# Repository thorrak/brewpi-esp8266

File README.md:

# BrewPi-ESP
An implementation of the BrewPi firmware on the ESP8266, ESP32, and ESP32-S2 with additional, added features

## Introduction
BrewPi provides a temperature controller which uses PID algorithms to tightly control a fermenting beer's temperature -- meaning that you can in many cases control the temperature of your fermenting beer to within _one tenth of a degree_. It was originally designed by Elco Jacobs, and used an Arduino running the BrewPi firmware to measure temperatures and toggle heating/cooling, paired with a Raspberry Pi to receive & graph temperature changes over time.

This project ports the BrewPi firmware to the ESP8266, ESP32, and ESP32-S2 controllers, eliminating the need for an Arduino. It is compatible with [Fermentrack 2/Fermentrack.net](https://www.fermentrack.net/), [legacy Fermentrack](http://www.fermentrack.com/) and [BrewPi-Remix](https://www.brewpiremix.com/) - the latter two of which can be installed on a Raspberry Pi to capture/graph temperatures similar to the original project.

> **Note:** ESP8266 support is deprecated as of the upcoming release. Existing ESP8266 builds will continue to receive bug fixes for a limited time, but new features will only target the ESP32 and ESP32-S2. For existing builds using the LoLin D1 Mini, the LoLin S2 Mini (ESP32-S2) is a pin-compatible replacement. See the [ESP8266 pinout](#esp8266) section below for more details.

### Documentation:
* [Selecting your Hardware](docs/source/Selecting%20an%20ESP%20Board.md)  
* [Building a "Solder Free" BrewPi](docs/source/Solder%20Free%20BrewPi.md)  
* [Installing the Firmware](docs/source/Installing%20the%20Firmware.md)
* [Hardware Information](https://github.com/thorrak/thorrak_hardware/tree/master/ESP8266%20BrewPi%20Boards) - PCB files, ordering and BOMs

## Configuration
Once you've flashed firmware to your ESP device, you'll need to configure it to connect to your WiFi network.  For that purpose, the firmware creates a WiFi access point named `BrewPiAP`, with a password of `brewpiesp`.  Connect to that access point and, if your device doesn't pull up a configuration page on its own, browse to `http://192.168.4.1`.  Then click on **Configure WiFi,** and configure it to connect to your WiFi network.

## Expected Pinout

### ESP32

There are two versions of the ESP32 firmware - one supporting an LCD2004 I2C display and one supporting a TFT. The pinout is slightly different between the two:

#### Common Pins

* 25 - Heat
* 26 - Cool
* 13 - OneWire Data
* 34 - Door

#### I2C Pins

* 21 - I2C SDA
* 22 - I2C SCL

#### TFT Pins

* 14 - TFT CS
* 27 - TFT DC
* 33 - TFT RST
* 12 - TS CS
* 32 - TFT Backlight

### ESP32-S2

* 5 - Heat
* 7 - Cool
* 9 - OneWire Data
* 11 - Door
* 33 - I2C SDA
* 35 - I2C SCL

### ESP8266 (Deprecated)

> **Deprecated:** ESP8266 support is deprecated and will not receive new features following v16. For existing builds using the LoLin D1 Mini, the [LoLin S2 Mini](https://www.aliexpress.us/item/3256802958877264.html) (ESP32-S2) is a pin-compatible drop-in replacement.

* D0 - Heat
* D1 - I2C SCL
* D2 - I2C SDA
* D5 - Cool
* D6 - OneWire Data
* D7 - Door (Untested)

## Supported Features
* OneWire Temperature Sensors
* SPIFFS configuration saving
* Pin-Based Relays
* WiFi Soft-AP Configuration
* OTA (WiFi) connection to BrewPi 
* I2C LCD (20x4) Screen (/w Address Autodetection)
* Tilt Hydrometer (as Temp Sensor) (ESP32 only)
* Inkbird Bluetooth temperature sensors (ESP32 only)
* TPLink Kasa WiFi Switches (ESP32 & ESP32-S2 WiFi only)
* HTTP interface for quick updates

## Currently Unsupported/Untested
* Rotary Encoder Support
* Door Sensor Support (Note - May work, untested)
* Buzzer Support
* OneWire "actuators"

## Differences vs. Arduino Implementation
The primary goal in creating this was to mirror the spirit of the Arduino implementation as closely as possible while adding in support for WiFi. That said, where I've needed to decide between preserving the original code and adapting for use with ESP controllers I've generally erred towards the latter. This is especially true with the EEPROM code - this implementation completely replaces the EEPROM with SPIFFS.

## Fermentrack Integration

Although this firmware works with brewpi-www, it is highly recommended that users use [Fermentrack 2/Fermentrack.net](https://www.fermentrack.net/) or [legacy Fermentrack](http://www.fermentrack.com/) instead as Fermentrack substantially reduces the work required to get an ESP-based controller working. Ongoing testing & support for this firmware is exclusively performed on Fermentrack and future changes may introduce incompatibility with brewpi-www.

## Hardware

I maintain a separate repo with PCB and 3D-printable case designs for all of my projects. It is available [here](https://github.com/thorrak/thorrak_hardware/).

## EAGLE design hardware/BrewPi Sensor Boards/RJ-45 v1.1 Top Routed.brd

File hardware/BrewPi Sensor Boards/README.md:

BrewPi Sensor Boards
====================

The BrewPi sensor boards are intended to allow for the DS18b20 temperature sensors (and optionally, door switch) to be connected to a PCB that is away from your main BrewPi controller, thereby allowing for the use of shorter temperature sensor cables - or for the placement of the sensor breakout inside your fermentation chamber if necessary. The sensor boards are then intended to be connected to the main controller board through the use of a cable.

There are two versions of the board, RJ-11 and RJ-45 -- however the RJ-45 version is recommended in nearly 100% of cases. 

* [RJ-45 Breakout Board](RJ-45%20Sensor%20Breakout.md)

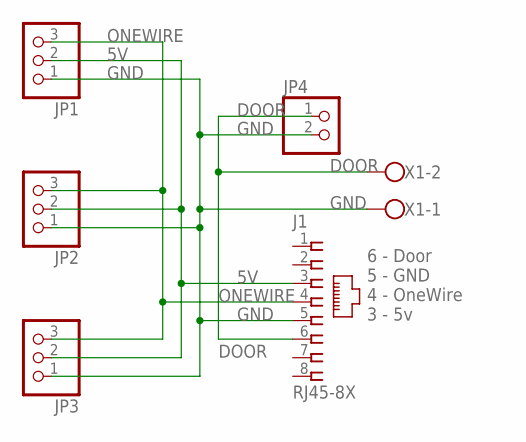
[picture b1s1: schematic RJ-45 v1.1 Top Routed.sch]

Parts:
J1: RJ45-8X; RJ45-NO-SHIELD
JP1, JP2, JP3: PINHD-1X3; 1X03
JP4: PINHD-1X2; 1X02
X1: W237-102

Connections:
5V: J1.3, JP1.2, JP2.2, JP3.2
DOOR: J1.6, JP4.1, X1.2
GND: J1.5, JP1.1, JP2.1, JP3.1, JP4.2, X1.1
ONEWIRE: J1.4, JP1.3, JP2.3, JP3.3

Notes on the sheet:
6 - Door 5 - GND 4 - OneWire 3 - 5v

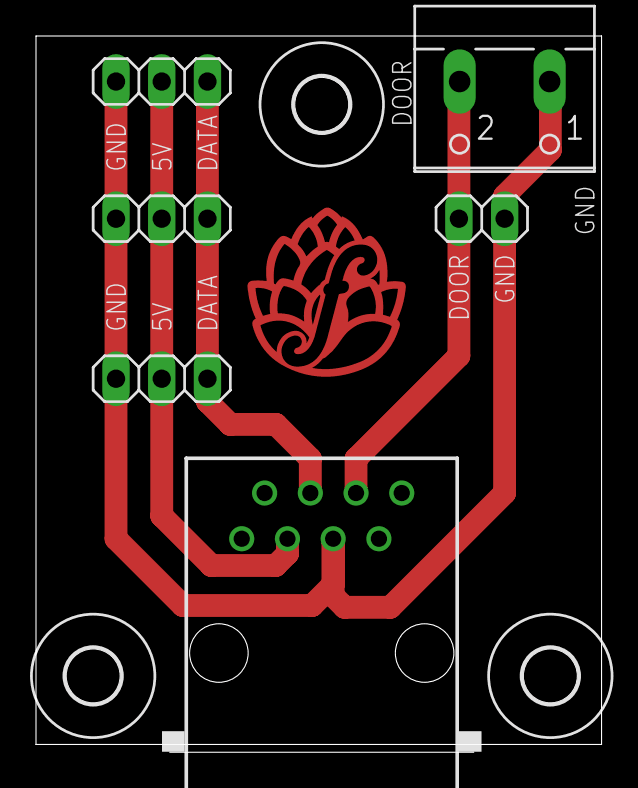
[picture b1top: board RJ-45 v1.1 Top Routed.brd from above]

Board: 2 copper layers, 31.4 x 39.8 mm, 9 parts (0 on the bottom side), 4 nets.

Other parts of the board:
U$1, U$2, U$3: 3,0

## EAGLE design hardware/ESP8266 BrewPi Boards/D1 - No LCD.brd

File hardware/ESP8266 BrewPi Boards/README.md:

ESP8266 BrewPi Controller Boards
================================

Although the "heart" of a BrewPi controller is the microprocessor running the BrewPi-compatible firmware, without other connected components that microcontroller cannot sense temperature, control power, or do any of the other things that make a temperature controller useful. Several PCBs have been designed to help simplify the wiring of the microcontroller to those other components.

Five different versions of the main PCB are listed here.  Each provide
different functionality and/or form factors:

*   No LCD Support with DuPont connectors and through-hole components
*   LCD Support with DuPont connectors and surface-mount level converter components
*   LCD Support with DuPont connectors, through-hole components, and a SparkFun-based level converter sub-board
*   LCD Support with screw connectors, through-hole components, and a SparkFun-based level converter sub-board
*   LCD Support with DuPont connectors, through-hole components, and an integrated level converter

You may either purchase the boards using the links provided through pcbs.io, or you may download and use the Eagle files provided with a board supplier of your choice.  If you use the pcbs.io links, Thorrak will receive a small credit on the site.

The BOM links provided are intended to serve as examples of the parts needed and are not the only place to source the parts listed.  Generally speaking, AliExpress is less expensive for parts.  The trade-off is that sometimes you are buying 100 at a time, and in most cases you are waiting for shipping.  Mouser or other project part suppliers will probably have these parts as well.

| Board Design                                                                             | Order Link                           | Through Hole       | Surface Mount      | I2C LCD            | Connector Type  | Integrated Level Shifter |
|------------------------------------------------------------------------------------------|--------------------------------------|--------------------|--------------------|--------------------|-----------------|--------------------------|
| Surface Mount                                                                            | [Order](https://PCBs.io/share/8DDk0) |                    | :heavy_check_mark: | :heavy_check_mark: | Dupont          | :heavy_check_mark:       |
| [TH - Sparkfun /w Dupont](D1%20-%20LCD%20TH%20Dupont.md)                                 | [Order](https://PCBs.io/share/40D1X) | :heavy_check_mark: |                    | :heavy_check_mark: | Dupont          |                          |
| [TH - MOSFETs](https://github.com/brewpi-remix/brewpi-pcb-rmx/tree/master/D1%20Breakout) | [Order](https://pcbs.io/share/z5JLZ) | :heavy_check_mark: |                    | :heavy_check_mark: | Dupont          | :heavy_check_mark:       |
| [TH - Sparkfun /w Screw Terminals](D1%20-%20LCD%20TH%20Screws.md)                        | [Order](https://PCBs.io/share/4qpVq) | :heavy_check_mark: |                    | :heavy_check_mark: | Screw Terminals |                          |
| [TH - No LCD](D1%20-%20No%20LCD.md)                                                      | [Order](https://PCBs.io/share/49yVo) | :heavy_check_mark: |                    |                    | Screw Terminals |                          |

Features Explained
------------------

### Through Hole vs. Surface Mount

Through Hole components generally have a wire or pin that goes through a hole on the PCB, enabling easy soldering on the back-side of the circuit board. By contrast, Surface Mount components are attached directly to the surface of a PCB with small dots of solder. The overwhelming majority of PCBs use primarily surface mount components - but as these are more difficult to solder by hand, many hobbyists prefer hand-soldering through hole components. 

Choose "surface mount" if you want a compact board and are comfortable with learning to solder surface mount components. Choose "through hole" if you are not comfortable soldering and would prefer the easiest option.

### I2C LCD

The ESP8266 port of the BrewPi firmware supports the utilization of a LCD screen connected via an "I2C" interface. Due to the nature of these LCD screens, this requires additional hardware which increases the size & complexity of the board - but the slight amount of additional pain when building the controller pays off in the increased utility of having an LCD display.

Choose this option if you want an LCD screen. Ignore this option if you prefer the cheapest board available (and are OK with not having an LCD display).

### Connector Type - Dupont vs. Screw Terminals

"Dupont" cables are a type of cable that has a single female header at each end. This allows for connecting two devices with "pin header" interfaces through the use of a compact "ribbon"-type cable. 

Boards that are "dupont" style have compact pin-headers on them, and can only be used with Dupont cables. By contrast, "screw terminal" style boards are designed to have screw terminals soldered on which makes attaching/detaching cables easier. Screw-terminal boards are larger but can be optionally used with pin headers as well, however "dupont" style boards are not compatible with screw terminals.

Choose "dupont" if you want a cheaper, smaller board. Choose "screw terminals" if you prefer much larger soldering pads. 

### Integrated Level Shifter

I2C LCDs require that the 3.3 volt logic from the ESP8266 be "translated" to the 5 volt logic required by the LCD. This is done through the use of a "level shifter". Level shifters are relatively simple components, but require soldering a number of things by hand which some hobbyists would prefer not to do. The boards with integrated level shifters have these additional components as part of the PCB, while those boards without an integrated level shifter use a "sparkfun"-style level shifter which is attached to the board using pin headers. 

Choose this option if you want a smaller, more compact board.

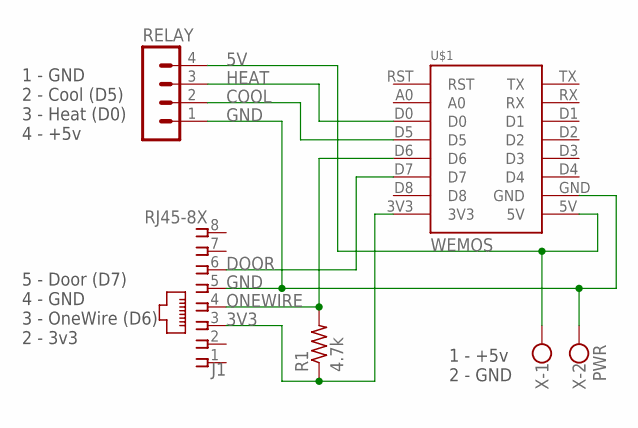
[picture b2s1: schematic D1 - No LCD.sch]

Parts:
J1: RJ45-8X; RJ45-NO-SHIELD
R1: 4.7k; 0309/12
RELAY: MA04-1
U$1: WEMOS
X: PWR; W237-102

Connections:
3V3: J1.3, R1.1, U$1.3V3
5V: RELAY.4, U$1.5V, X.1
COOL: RELAY.2, U$1.D5
DOOR: J1.6, U$1.D7
GND: J1.5, RELAY.1, U$1.GND, X.2
HEAT: RELAY.3, U$1.D0
ONEWIRE: J1.4, R1.2, U$1.D6

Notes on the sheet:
1 - GND 2 - Cool (D5) 3 - Heat (D0) 4 - +5v
5 - Door (D7) 4 - GND 3 - OneWire (D6) 2 - 3v3
1 - +5v 2 - GND

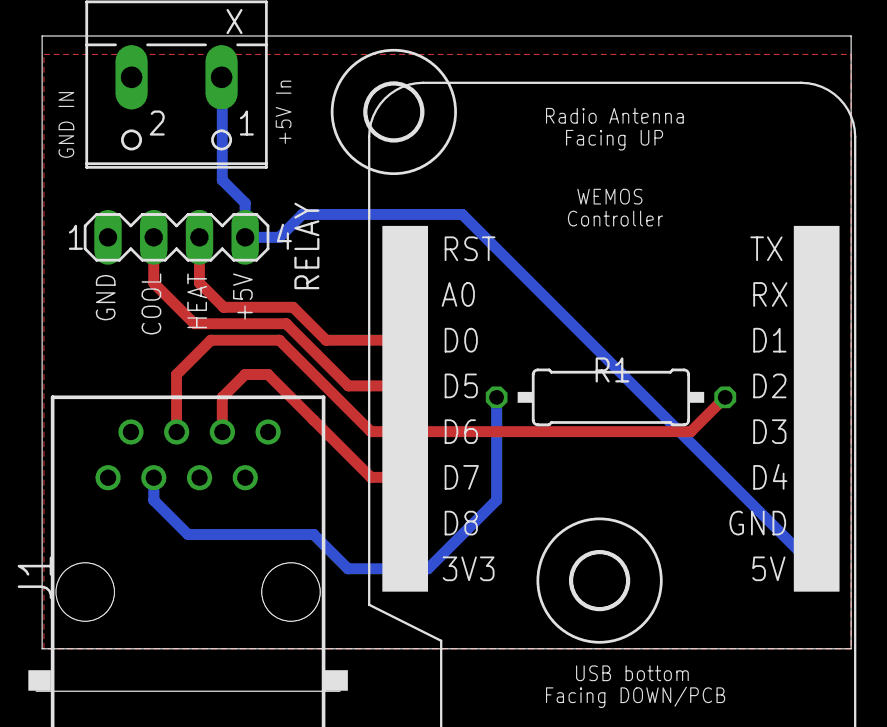
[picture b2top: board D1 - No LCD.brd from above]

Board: 2 copper layers, 45.3 x 36.4 mm, 7 parts (0 on the bottom side), 7 nets.

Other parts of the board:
U$4, U$5: 3,0

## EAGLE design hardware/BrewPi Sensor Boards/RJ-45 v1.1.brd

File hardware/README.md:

# Hardware

In the interest of streamlining updates to the PCBs, I've broken all of my "hardware" out into its own repo. For hardware related to this project, please visit:

https://github.com/thorrak/thorrak_hardware/blob/master/BrewPi-ESP8266.md

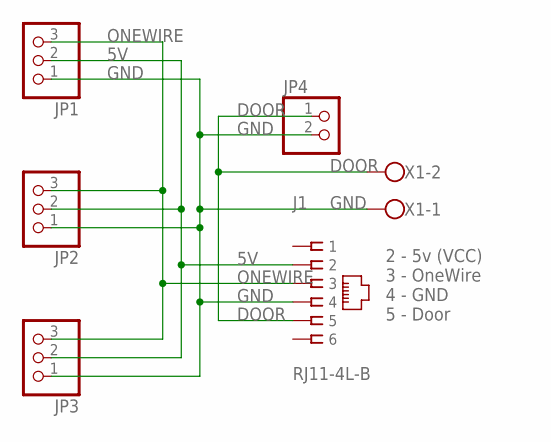
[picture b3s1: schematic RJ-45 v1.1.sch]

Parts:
J1: RJ11-4L-B; RJ11-NO_SHIELD
JP1, JP2, JP3: PINHD-1X3; 1X03
JP4: PINHD-1X2; 1X02
X1: W237-102

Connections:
5V: J1.2, JP1.2, JP2.2, JP3.2
DOOR: J1.5, JP4.1, X1.2
GND: J1.4, JP1.1, JP2.1, JP3.1, JP4.2, X1.1
ONEWIRE: J1.3, JP1.3, JP2.3, JP3.3

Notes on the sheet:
2 - 5v (VCC) 3 - OneWire 4 - GND 5 - Door

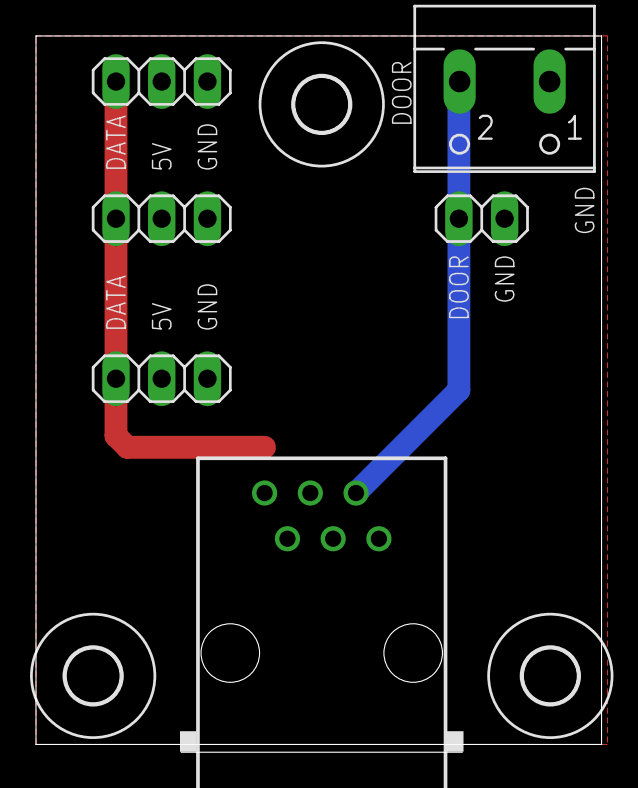
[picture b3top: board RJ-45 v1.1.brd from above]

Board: 2 copper layers, 31.4 x 39.8 mm, 9 parts (0 on the bottom side), 4 nets.

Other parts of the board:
U$1, U$2, U$3: 3,0

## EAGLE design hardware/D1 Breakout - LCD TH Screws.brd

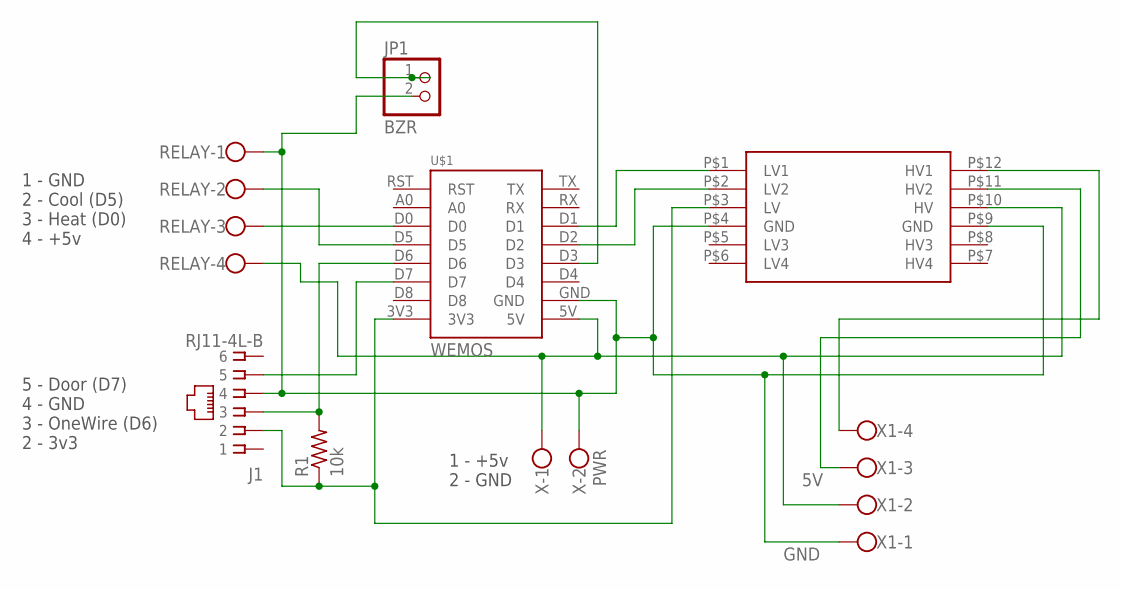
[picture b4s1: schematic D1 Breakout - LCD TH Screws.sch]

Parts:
J1: RJ11-4L-B; RJ11-NO_SHIELD
JP1: BZR; 1X02
R1: 10k; 0207/5V
RELAY: W237-4
U$1: WEMOS
U$3: SPARKFUN-BOARDS_LOGIC_LEVEL_CONVERTER
X: PWR; W237-102
X1: W237-4

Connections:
5V: RELAY.4, U$1.5V, U$3.P$10 (HV), X.1, X1.2
D0: RELAY.3, U$1.D0
D5: RELAY.2, U$1.D5
D6: J1.3, R1.2, U$1.D6
D7: J1.5, U$1.D7
GND: J1.4, JP1.2, RELAY.1, U$1.GND, U$3.P$4 (GND), U$3.P$9 (GND), X.2, X1.1
unnamed: U$1.D1, U$3.P$1 (LV1)
unnamed: U$1.D2, U$3.P$2 (LV2)
unnamed: J1.2, R1.1, U$1.3V3, U$3.P$3 (LV)
unnamed: U$3.P$12 (HV1), X1.4
unnamed: U$3.P$11 (HV2), X1.3
unnamed: JP1.1, U$1.D3

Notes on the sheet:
1 - GND 2 - Cool (D5) 3 - Heat (D0) 4 - +5v
5 - Door (D7) 4 - GND 3 - OneWire (D6) 2 - 3v3
1 - +5v 2 - GND

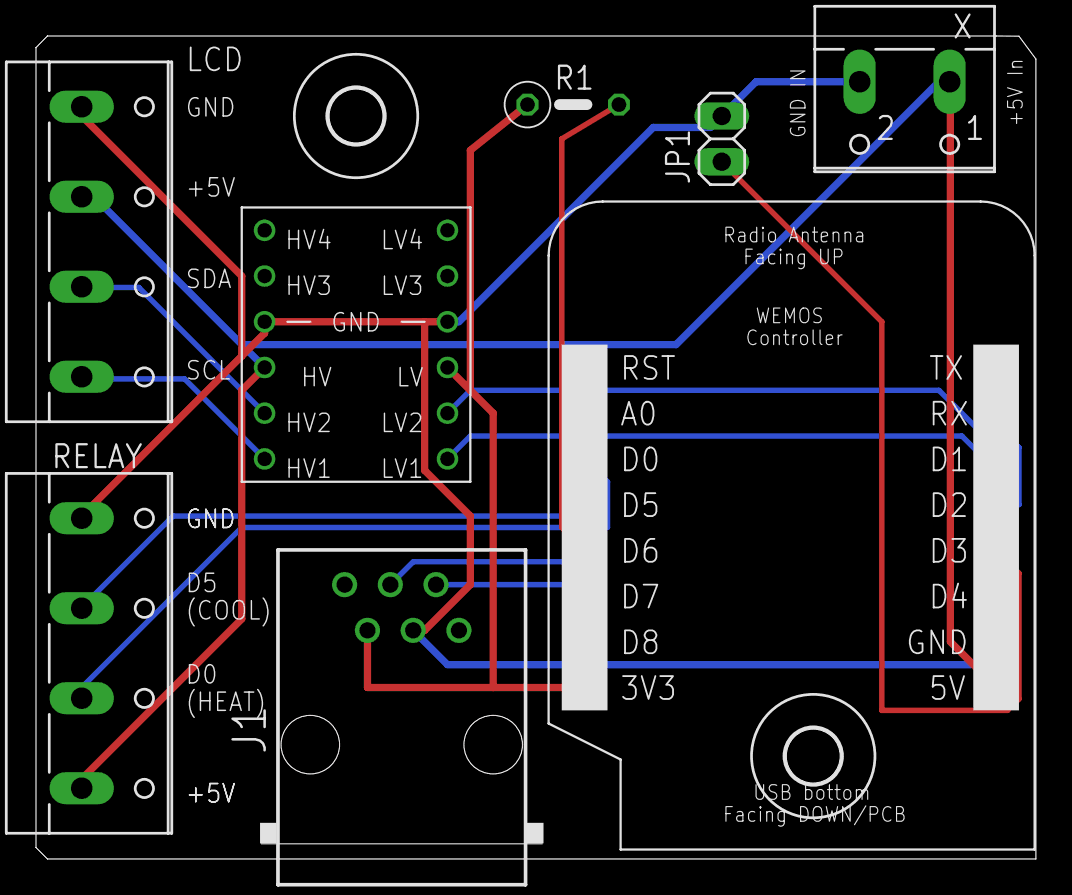
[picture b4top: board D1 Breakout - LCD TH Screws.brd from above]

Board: 2 copper layers, 55.5 x 45.7 mm, 10 parts (0 on the bottom side), 12 nets.

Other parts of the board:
U$2, U$4: 3,0

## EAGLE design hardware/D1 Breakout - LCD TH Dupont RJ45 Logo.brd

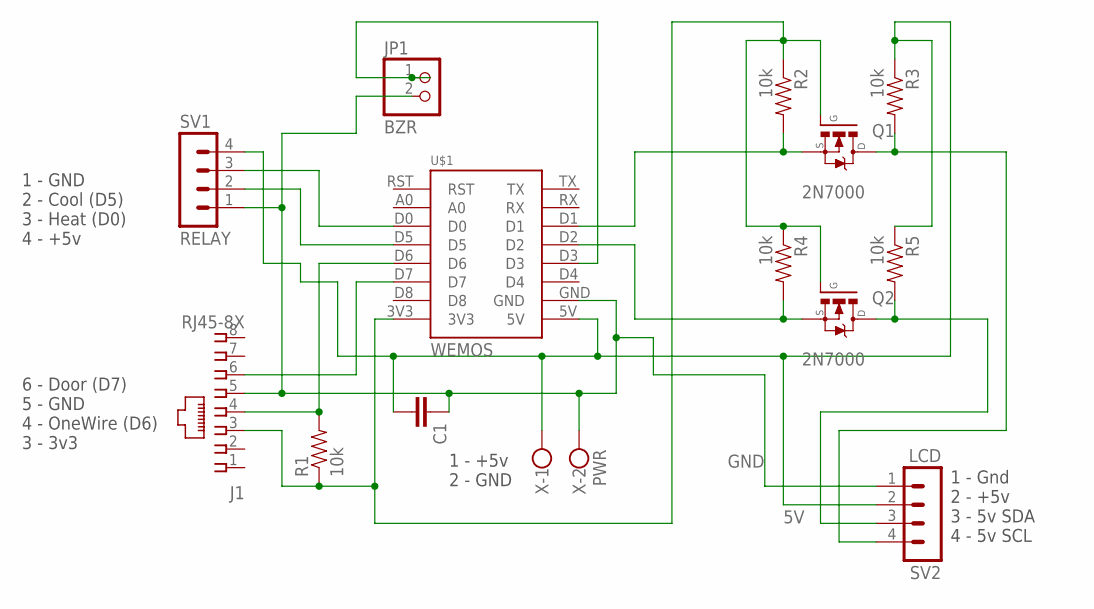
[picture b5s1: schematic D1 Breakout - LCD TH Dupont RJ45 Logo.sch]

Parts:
C1: 100uF; C5B3
J1: RJ45-8X; RJ45-NO-SHIELD-NOLINE
JP1: BZR; 1X02
Q1, Q2: 2N7000; TO-92
R1, R2, R3, R4, R5: 10k; AXIAL-0.3
SV1: RELAY; MA04-1
SV2: LCD; MA04-1
U$1: WEMOS
X: PWR; W237-102

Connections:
3V3: J1.3, Q1.2 (G), Q2.2 (G), R1.P$1 (1), R2.P$1 (1), R4.P$1 (1), U$1.3V3
5V: C1.2, R3.P$1 (1), R5.P$1 (1), SV1.4, SV2.2, U$1.5V, X.1
5V_SDA: Q2.3 (D), R5.P$2 (2), SV2.3
D6: J1.4, R1.P$2 (2), U$1.D6
D7: J1.6, U$1.D7
GND: C1.1, J1.5, JP1.2, SV1.1, SV2.1, U$1.GND, X.2
unnamed: Q2.1 (S), R4.P$2 (2), U$1.D2
unnamed: Q1.1 (S), R2.P$2 (2), U$1.D1
unnamed: JP1.1, U$1.D3
unnamed: SV1.2, U$1.D5
unnamed: SV1.3, U$1.D0
SCL5V: Q1.3 (D), R3.P$2 (2), SV2.4

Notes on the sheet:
1 - GND 2 - Cool (D5) 3 - Heat (D0) 4 - +5v
6 - Door (D7) 5 - GND 4 - OneWire (D6) 3 - 3v3
1 - +5v 2 - GND
1 - Gnd 2 - +5v 3 - 5v SDA 4 - 5v SCL

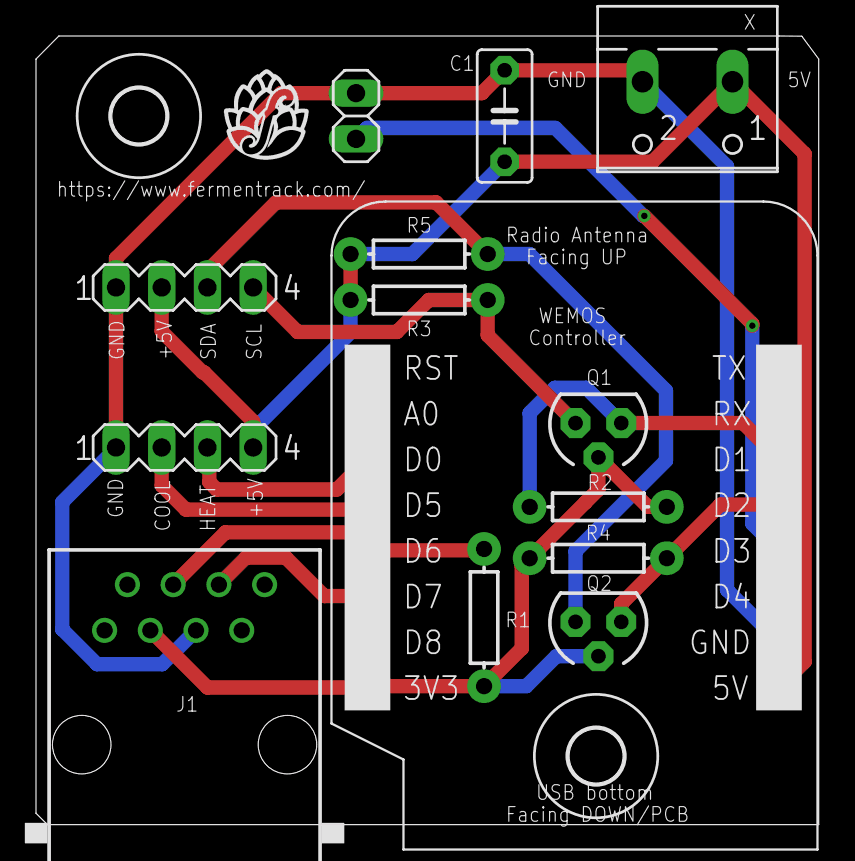
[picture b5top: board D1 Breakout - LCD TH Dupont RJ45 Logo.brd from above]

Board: 2 copper layers, 43.5 x 43.8 mm, 16 parts (0 on the bottom side), 12 nets.

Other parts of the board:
U$2, U$4: 3,0

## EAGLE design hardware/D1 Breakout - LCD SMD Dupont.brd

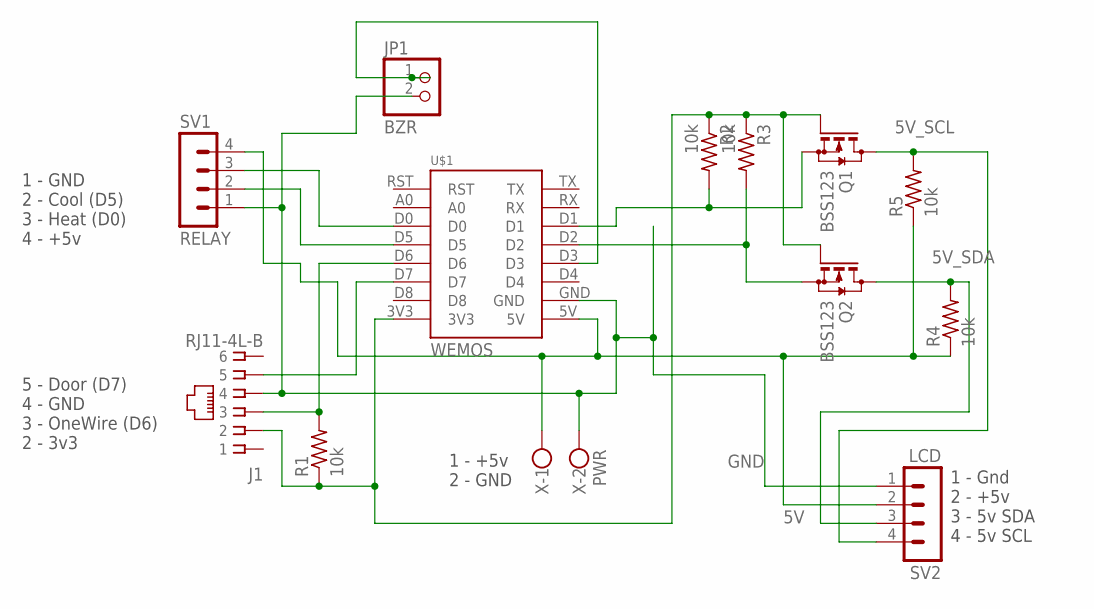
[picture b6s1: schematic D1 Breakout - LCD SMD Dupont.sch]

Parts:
J1: RJ11-4L-B; RJ11-NO_SHIELD
JP1: BZR; 1X02
Q1, Q2: BSS123; SOT23
R1, R2, R3, R4, R5: 10k; R0805
SV1: RELAY; MA04-1
SV2: LCD; MA04-1
U$1: WEMOS
X: PWR; W237-102

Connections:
3V3_SCL: Q1.2 (S), R2.2, U$1.D1
3V3_SDA: Q2.2 (S), R3.2, U$1.D2
5V: R4.1, R5.1, SV1.4, SV2.2, U$1.5V, X.1
5V_SCL: Q1.3 (D), R5.2, SV2.4
5V_SDA: Q2.3 (D), R4.2, SV2.3
D6: J1.3, R1.2, U$1.D6
D7: J1.5, U$1.D7
GND: J1.4, JP1.2, SV1.1, SV2.1, U$1.GND, X.2
unnamed: J1.2, Q1.1 (G), Q2.1 (G), R1.1, R2.1, R3.1, U$1.3V3
unnamed: JP1.1, U$1.D3
unnamed: SV1.2, U$1.D5
unnamed: SV1.3, U$1.D0

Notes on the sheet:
1 - GND 2 - Cool (D5) 3 - Heat (D0) 4 - +5v
5 - Door (D7) 4 - GND 3 - OneWire (D6) 2 - 3v3
1 - +5v 2 - GND
1 - Gnd 2 - +5v 3 - 5v SDA 4 - 5v SCL

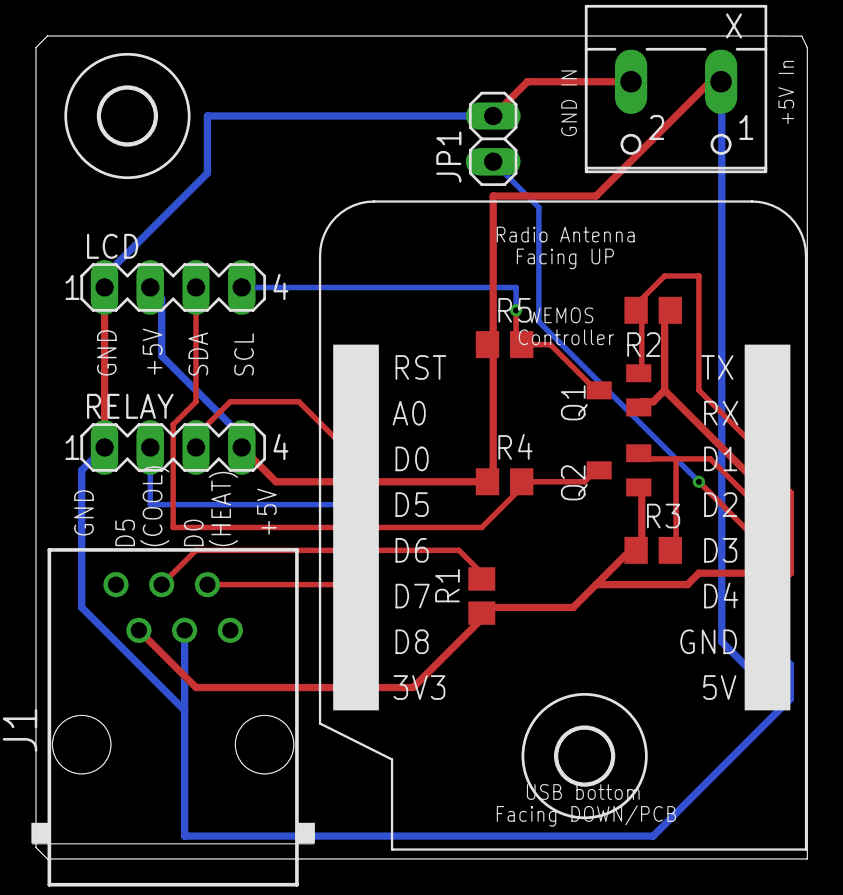
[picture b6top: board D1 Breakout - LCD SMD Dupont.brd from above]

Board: 2 copper layers, 42.8 x 45.7 mm, 15 parts (0 on the bottom side), 12 nets.

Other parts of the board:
U$2, U$4: 3,0

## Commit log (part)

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2020-10-18 Add WiFi information command
    Adds the 'W' command, which will dump the current connection's SSID &
    signal strength.
    Also improves some doxygen comments in ESP_WiFi.*
2020-10-19 Add prometheus http endpoint
2021-02-25 Update platformio to latest version & add lowdelay firmware version
2021-05-21 Swap SPIFFS for LittleFS for ESP8266 builds
2021-05-21 Update lowdelay firmware
2021-05-25 Replace bitwise xor with explicit comparisons
2021-05-27 Do proper fixed point and tempdiff conversions
2021-06-04 Refactor "eeprom" reset code
2022-02-05 Refactor DeviceConfig
2022-02-19 Add delay to prevent race condition Active scanning causes us to attempt to connect to devices as they are located. If we begin a connection to a device, stop scanning, start scanning again, and then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
2022-02-19 Add support for Tilt Hydrometers
2022-02-21 Fix output of values on hardware enumeration
2022-03-07 Initial TPLink support
2022-03-09 Require confirmation of eeprom reset
2022-03-10 Add Tilt color to hardware response
2022-03-10 Bugfixes and cleanup
2022-03-10 TFT LCD display enhancements
2022-03-10 Fix ESP8266 compilation
2022-03-19 Initialize a data partition Although we don't need to do this, it will eliminate the need to reset the eeprom immediately after installation.
2022-03-19 Add confirmation requirement to EEPROM reset
2022-03-20 Roll back further for ESP8266 WiFi bug
2022-03-21 Add StreamBuffer alternate implementation Some frameworks (e.g. ESP32 currently) crash when calling wifi.flush() which leads to StreamUtils not working. This buffers in a C String instead, outputting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
2022-03-24 Cache devices in memory
2022-03-24 Deactivate actuator on uninstall (Fixes #62)
2022-03-25 Clean up TFT code
2022-04-05 Update discovery payload for newer HS103s
2022-04-06 Add safety timeout to TPLink switches
2022-04-06 Explicitly reconnect to WiFi when disconnected (Closes #23)
2022-04-06 Eliminate warning
2022-04-10 Fix degree symbol on pseudo-LCD
2022-04-11 Print IP address on TFT display
2022-07-10 Finish support for ESP32-S2
2023-02-20 Refactor out JSON creation
2023-02-20 Fix Upstream Settings
2023-02-21 Fix JSON serialization of chars Resolves incompatibility with ArduinoJSON 6.20+
2023-02-22 Move `readJsonIntoHardwareSpec` out of `enumerateHardware`
2023-02-22 Fix sendSingleItemJsonMessage This previously was not properly accounting for `PiLink::bufferPrints` which resulted in the prefix becoming a suffix.
2023-02-22 Don't pass things by reference unnecessarily
2023-02-22 Better handle device caching
2023-02-25 Async HTTP server build
2023-02-25 Convert from AsyncWebServer to WebServer
2023-02-25 Reducing MAX_DEVICES Slots are only used for configured devices - so we're limited to the number of functions we can set. Adding a few more for future gravity sensor support
2023-02-25 Add sensor assignment endpoint
2023-02-25 Fix invalid temp whitespace
2023-02-25 Update for latest ESP8266 Arduino framework
2023-02-25 Ignore errors if missing .bins
2023-02-25 Break out build jobs
2023-02-25 Break FS build out again
2023-02-25 Add GH Actions for compilation
    * Update for latest ESP8266 Arduino framework
    * Create GH Actions Auto-builder
2023-02-25 Fix padding around calibration offsets
2023-02-25 Apply calibration offset to Inkbird & Tilt sensors
2023-02-25 Remove serial debugging
2023-02-25 Minor display fixes
2023-02-26 Allow invert to be provided as a proper bool
2023-02-28 Add "set mode" endpoint
2023-03-01 Properly handle extended settings updates
2023-03-01 Also serve vue paths without trailing slash
2023-03-01 Send human readable alias for pin devices
2023-03-01 Enable HTTP interface for WiFi controllers
2023-03-01 Update docs
2023-03-02 Make lowDelay mode an extended setting
2023-03-02 Update min times before initializing temp control
2023-03-02 Update lowDelay toggle in UI
2023-03-03 Update documentation
2023-03-07 Restart on bluetooth failure
2023-03-18 Shift display away from static
2023-03-19 Eliminate duplicative lowDelay extendedSetting
2023-03-23 Revert 00bc5bf
2023-03-26 Create initial data sender
2023-03-26 Build on push to master
2023-03-29 Add `isRegistered` to `UpstreamSettings`
2023-04-08 Fix `flush()` in Espressif's WiFiClient
2023-04-08 If the user saves, always reattempt registration
2023-04-08 Change api_key to apiKey
2023-04-20 Update REST message handler
2023-04-21 Add "refresh config" message
2023-04-22 Fix value serialization
2023-04-22 Process incoming device assignments
2023-06-18 Reduce scan fail threshhold
2023-06-23 Lock ESP32-S2 targets to Arduino v2.0.6 Arduino versions past v2.0.6 are based on ESP-IDF v4.4.4 which introduces a bug in the IIC implementation causing delays in every write to IIC LCDs. Reverting 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
2023-07-16 deploy: f4bdca9ca48afab4fe6f4af8ca12d954e4e5895c
2023-08-20 Send mode as part of status payload
2023-09-06 Add I2C workaround for ESP32-S2
2023-09-10 deploy: 0842f97cbbddf193a87a59ed685471017beea0b6
2023-09-16 Change key for mode changes to newMode
2023-09-16 Process temperature updates in status response
2023-10-25 deploy: 54f8163d78b5daf0adc4c1adeec6a87dfb5b0fb8
2023-11-08 Check for both type and mic type (Fixes #104)
2023-11-08 Fix logical errors in new Kasa detection (#104)
2023-11-12 Ignore telnet connections when using REST When configured to use FT's REST interface, don't connect telnet clients
2024-01-03 Prevent reads on disconnected sensors
2024-01-20 Change reset_wifi to reset_connection
2024-01-22 Replace negative TFT checks with positive IIC checks There were a number of instances where I was checking for the absence of the TFT flag rather than the presence of the IIC flag to enable IIC funct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
2024-01-22 Add _ILI to DisplayTFT in preparation for new driver
2024-01-26 Add eSPI display driver
2024-01-26 Minor cleanup of unused variables
2024-01-26 Lock library versions
2024-01-26 Have GitHub action build prerelease branch
2024-01-26 Update actions versions
2024-01-26 Add firmware version to config message
2024-02-01 Fix eSPI TFT support
2024-02-02 Track gravity from Tilt beer sensor
2024-02-02 Rename "gravity" to "gravity_raw" in message
2024-08-11 Update to Arduino 3.x core for ESP32
2024-08-11 Re-enable logging of bluetooth disconnects One of the benefits I hope to get from the Arduino 3.x core is fixing the "silent bluetooth failure" bug I had previously experienced with active scanning. 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
2024-08-23 Fix persistant WiFi disconnects on ESP8266
2024-08-28 Update WiFiManager version
2024-12-14 Create inkbird sensors for both internal and external probes Only the primary probe was being created for Inkbird sensors -- This explicitly splits internal and external for sensors that have both.
2024-12-14 Update docs and version
2024-12-14 Fix eSPI support
2024-12-14 Refactor all prints to use printAtMonoChars
2024-12-14 Print IP address info on screen
2024-12-14 Clean up LCD caching, fix temp display
2024-12-14 Clean up
2024-12-15 Conditional defines for ESP8266 support
2024-12-15 Don't pad eSPI displays when already full
2024-12-15 Prevent potential filter poisoning
2024-12-16 Update to use latest NimBLE Library
2025-01-02 Switch to pioarduino Changes from platformio to pioarduino, and updates to Arduino 3.10.0
2025-01-07 Convert `Serial.print` statements to use ArduinoLog instead
2025-02-20 Update README.md
    Updated link for ESP8266 board. Added additional link for ESP32 board. Added general link to all hardware repo.
2025-02-23 Reset the screen when pin-based actuators toggle Pin-based relays introduce significant noise in the power that is being supplied to the screen, and can cause the screen to freeze/scramble. This re-i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
2025-02-25 Reduce chance for Inkbird sensor to disappear This makes two changes - Extending the timeout for Inkbird sensors to 62 seconds, and change the scan restart frequency to 10 seconds
2025-02-25 Convert ESP32 from SPIFFS to LittleFS
2025-02-25 Update GH actions builder
2025-02-25 Split build steps
2025-02-26 Update README.md
    fixed a typo in one of the links that caused a markdown formatting error
2025-03-01 Convert from WebServer back to AsyncWebServer
2025-03-01 Don't process device definition updates asynchronously The DallasTemperature library blocks when reading sensors, which causes the async web server to crash. This change creates the device definition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
2025-03-01 Update UI for Async changes
2025-03-01 Add sdkconfig files
2025-03-01 Add option to enable/disable resetting on pin toggle (Closes #123)
2025-03-02 Clean up file formatting
2025-04-07 v16 beta 1 prep
2025-11-29 Begin implementing glycol mode support
2025-11-29 Change whitespace
2025-11-30 Adjust display for glycol mode
2025-12-01 Add new ESP-IDF-based OW libraries
2025-12-01 Use Espressif library for ESP32
2025-12-01 Refactor OneWire pin configuration to use a single oneWirePin definition, removing beerSensorPin and fridgeSensorPin support
2025-12-01 Update GH Action
2025-12-03 Convert from PID to bang-bang implementation for Glycol
2025-12-07 Add optional logging for glycol state transitions
2025-12-10 Write twice during preload
2025-12-10 Initial plan
2025-12-10 Add comprehensive task summary and update documentation
2025-12-10 Add PR overview document
2025-12-10 Add esp-idf config files to gitignore
2025-12-13 Allow setting control constants from UI
    This is primarily to enable changing the temperature units from within the UI (Closes #132)
2025-12-21 Enhance DS18B20 sensor handling with reset detection and conversion improvements
    - Added functions for reading and writing scratchpad data
    - Implemented reset detection mechanism for ESP32 in ds18b20_init_connection
    - Introduced non-blocking temperature conversion for multiple sensors for ESP32
    - Updated OneWireTempSensor class to track conversion failures and handle power-on defaults
2025-12-28 Add slight delay before starting webserver Resolves race condition at initial controller boot
2025-12-28 Update UI files
2026-01-18 Add device name handling to registration process
2026-02-14 Update docs for v16 release
2026-02-14 Replace Arduino APIs with ESP-IDF equivalents (Phase 1)
    Remove F() macro, replace delay() with vTaskDelay(),
    millis() with esp_timer, yield() with vTaskDelay(1),
    and ESP.* system calls with esp_restart/esp_get_free_heap_size/
    esp_efuse_mac_get_default.
2026-02-14 Replace Arduino String with std::string and char buffers
2026-02-15 Replace ESPmDNS with native mdns, update build config
2026-02-15 Replace Wire.h with ESP-IDF i2c_master driver
2026-02-15 Replace ESPAsyncWebServer with ESP-IDF esp_http_server
2026-02-15 Switch to Arduino as an esp-idf component
2026-02-15 Remove ESP8266 support
2026-02-15 Rename brewpi-esp8266.cpp to main.cpp
2026-02-15 Eliminate progmem
2026-02-15 Replace AXP192 driver
2026-02-15 Initial Lovyan conversion
2026-02-16 Fix Lovyan config
2026-03-17 Add glycol control HTML page and update server routing
2026-03-28 Use WiFi Manager Custom UI
2026-03-28 Fix include casing
2026-03-28 Increase main task stack size and fix eSPI pin assignment
2026-03-29 feat(api): allow updating glycol heating PID constants
2026-04-05 Convert from esp_wifi_manager to esp_wifi_config
2026-04-06 Fixes for DS18b20 Temp Sensors
2026-04-20 Move TempControl mode wiring out of the control flow
2026-04-20 Refactor Fermentrack communication
2026-04-20 Integrate web UI source and auto-build on buildfs
    Move the Vue/Vite UI (previously in a separate brewpi_esp_ui repo) into
    ui/ and generate its artifacts on demand via scripts/build_ui.py, which
    PlatformIO runs as a pre-action on the filesystem-image target. Firmware
    builds are unaffected; buildfs/uploadfs rebuild and copy ui/dist/* into
    data/ before mklittlefs runs. The six generated artifacts are now
    gitignored since they're rebuilt on demand.
2026-04-21 Initialize TempControl before bringing up WiFi
    The async HTTP server starts answering requests as soon as WiFi
    associates, but TempControl::beerSensor and fridgeSensor are static
    TempSensor* members that remain NULL until TempControl::init() allocates
    default disconnected sensors. A browser auto-refresh during boot would
    dispatch /api/all_temp_control/ into printTemperaturesJson(), which
    dereferences beerSensor->isConnected() and crashes with a LoadProhibited
2026-04-21 Quiet OneWire log spam on empty or failing buses
    Two sources of repeating log noise on buses that fail to enumerate any
    devices:
    - The ESP-IDF 1-wire device iterator logs "reset bus failed: no devices
    found" at WARN on every scan. Demote that tag to ERROR so an empty
    bus stays silent at the ESP-IDF layer.
    - OneWireTempSensor::init() is called on every 1Hz tick while a sensor
2026-04-26 Fix Fermentrack 2 connection edge cases
2026-05-01 Enable BLE WiFi configuration
2026-05-01 Fix version number
2026-05-01 Disable BLE for S2

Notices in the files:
parts and their libraries:
SparkFun-Resistors: Licensing: Creative Commons ShareAlike 4.0 International - https://creativecommons.org/licenses/by-sa/4.0
